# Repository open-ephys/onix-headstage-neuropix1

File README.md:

# ONIX Neuropixels-1.0 Headstage
Serialized, multifunction headstage targeting the [Neuropixels 1.0
probe](https://www.neuropixels.org/probe). This headstage supports:

- Two Neuropixels 1.0 probes
- A BNO055 9-axis IMU for real-time, 3D orientation tracking
- Three TS4231 light to digital converters for real-time, 3D position tracking
  with HTC Vive base stations
- A high performance MAX10 FPGA for real-time processing and probe data
  correction (offset removal and gain correction)

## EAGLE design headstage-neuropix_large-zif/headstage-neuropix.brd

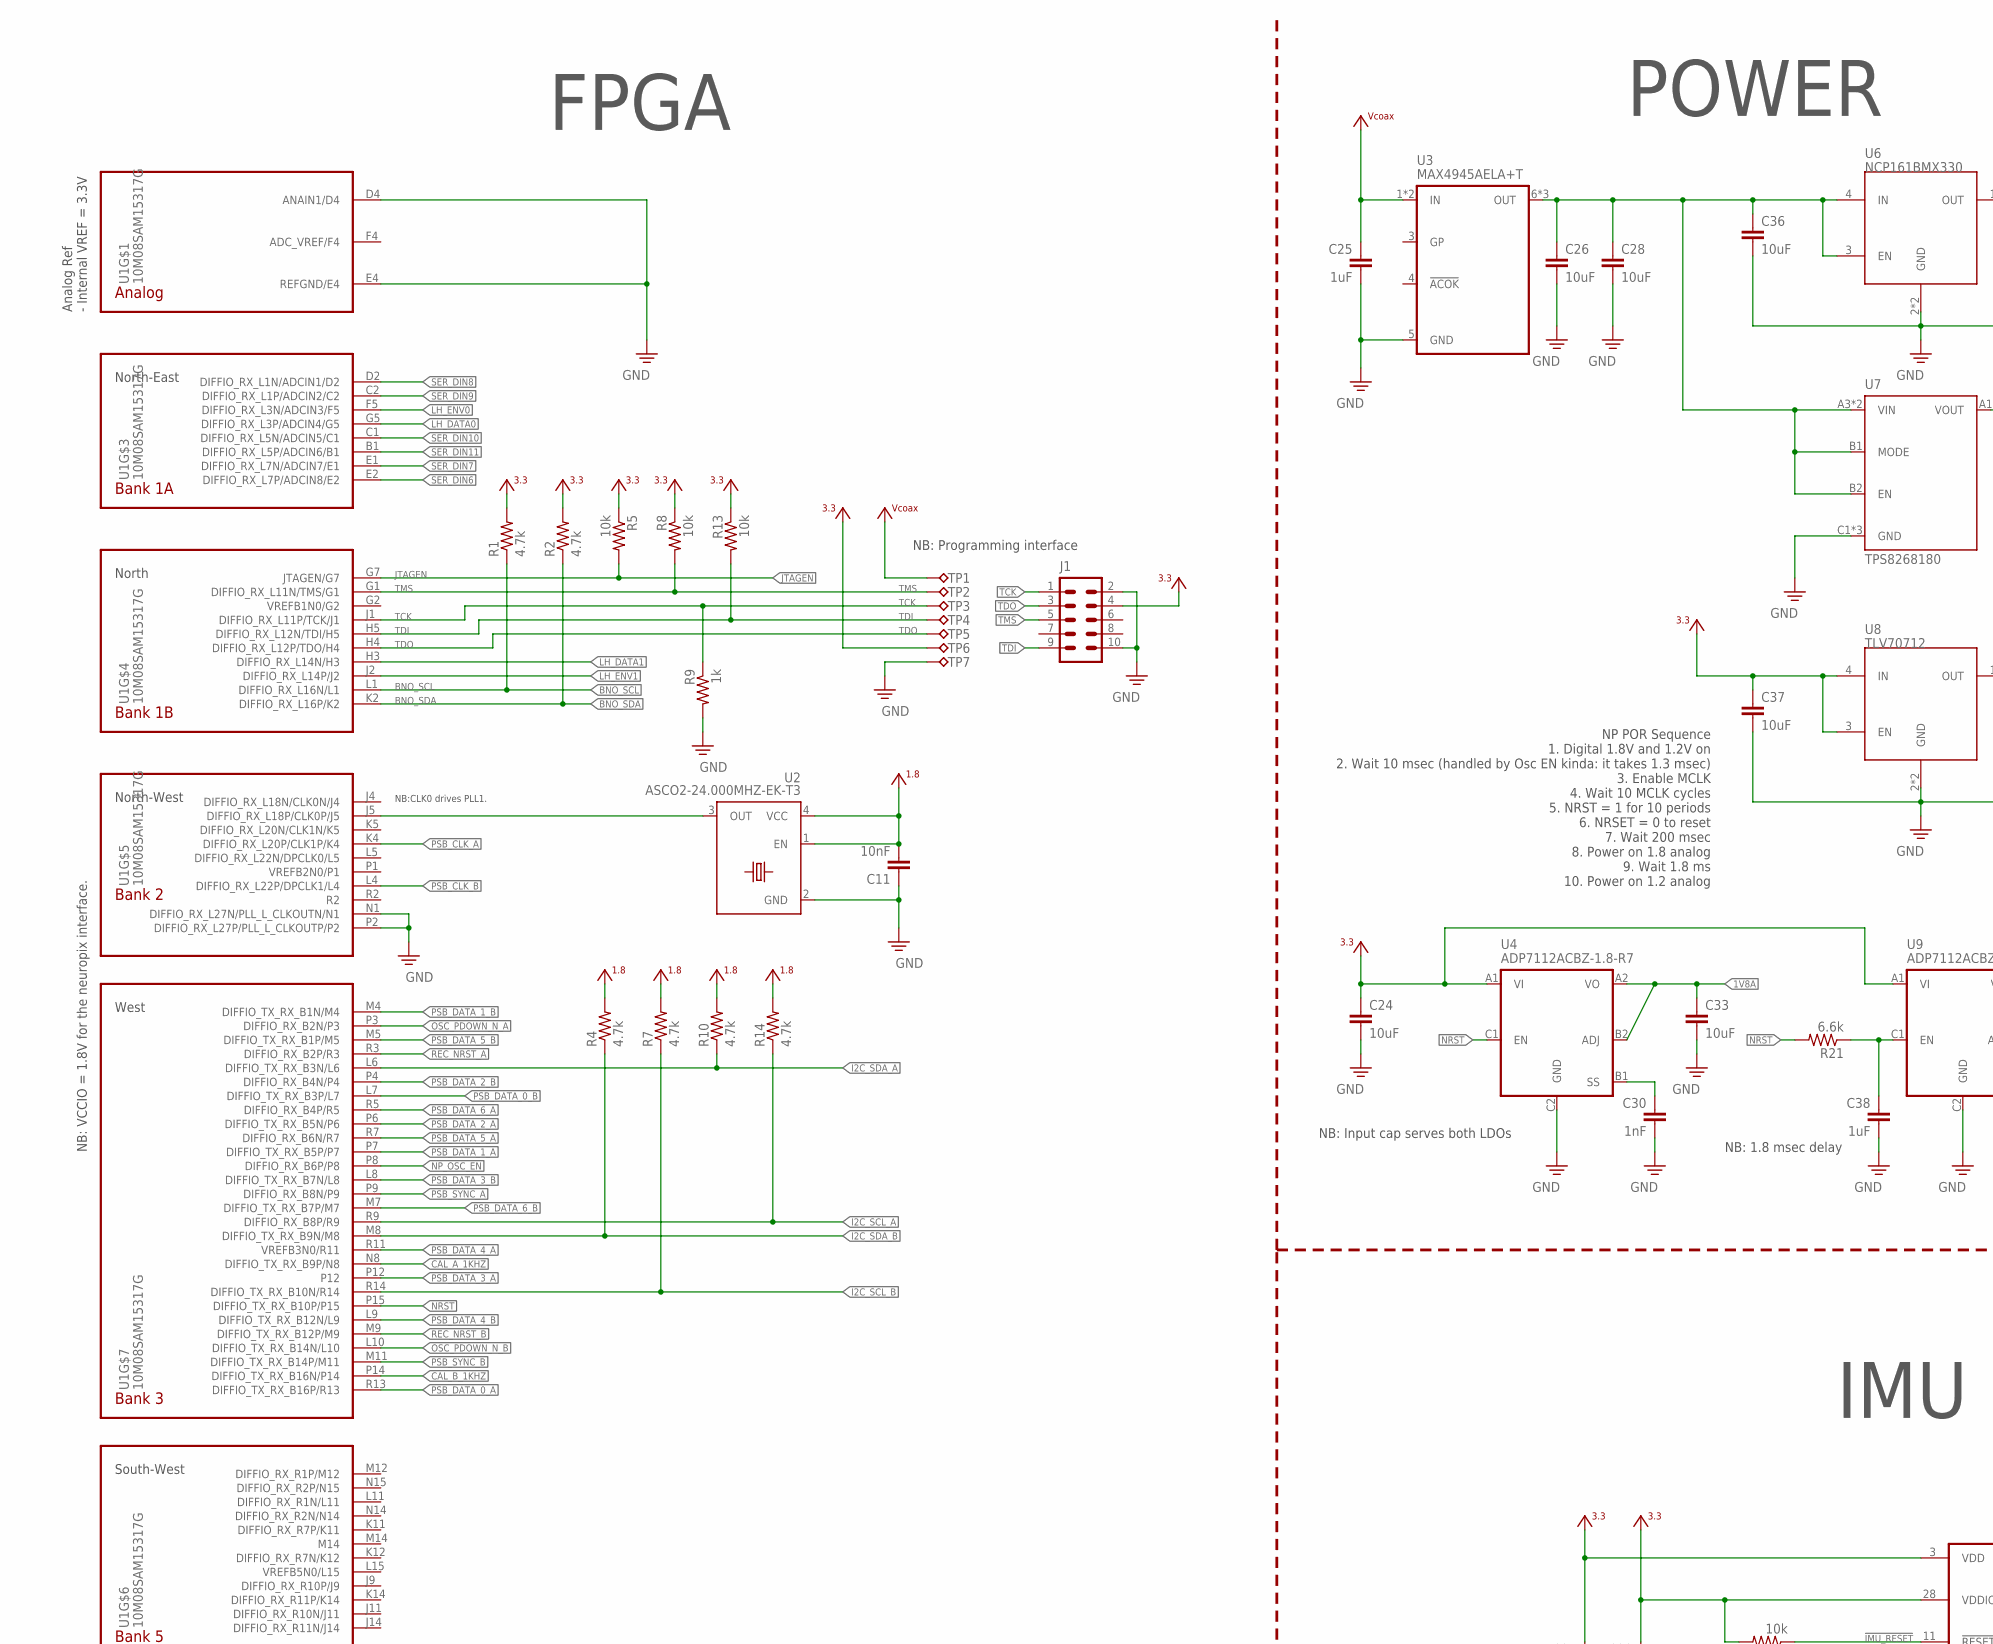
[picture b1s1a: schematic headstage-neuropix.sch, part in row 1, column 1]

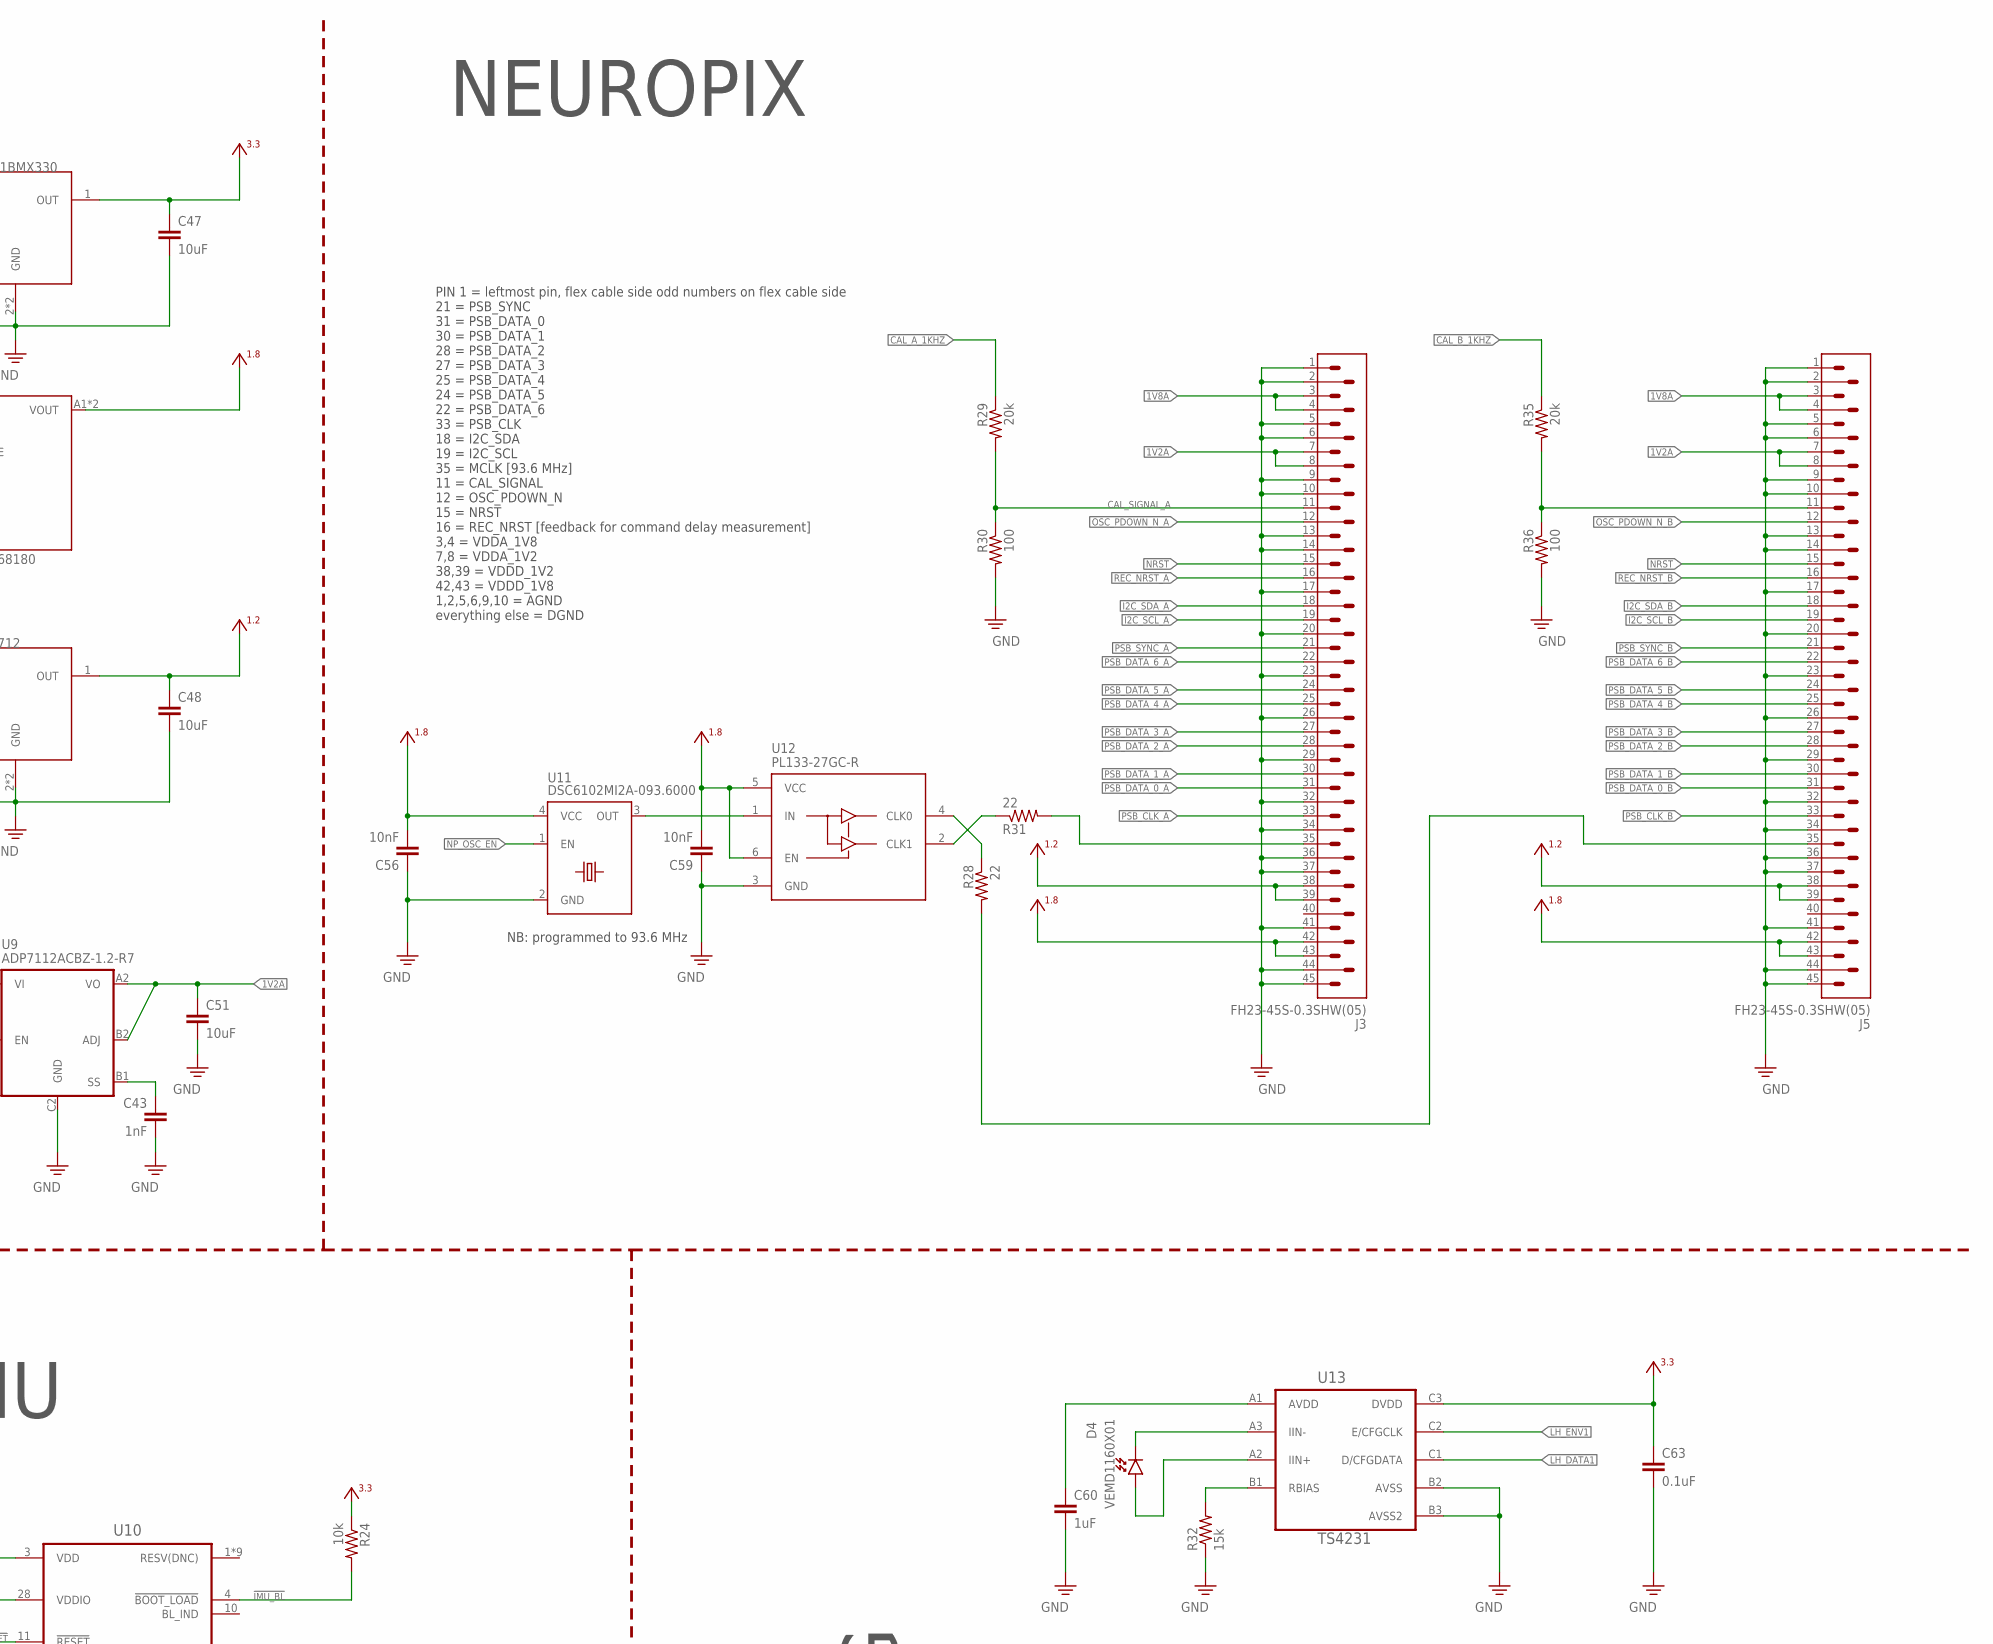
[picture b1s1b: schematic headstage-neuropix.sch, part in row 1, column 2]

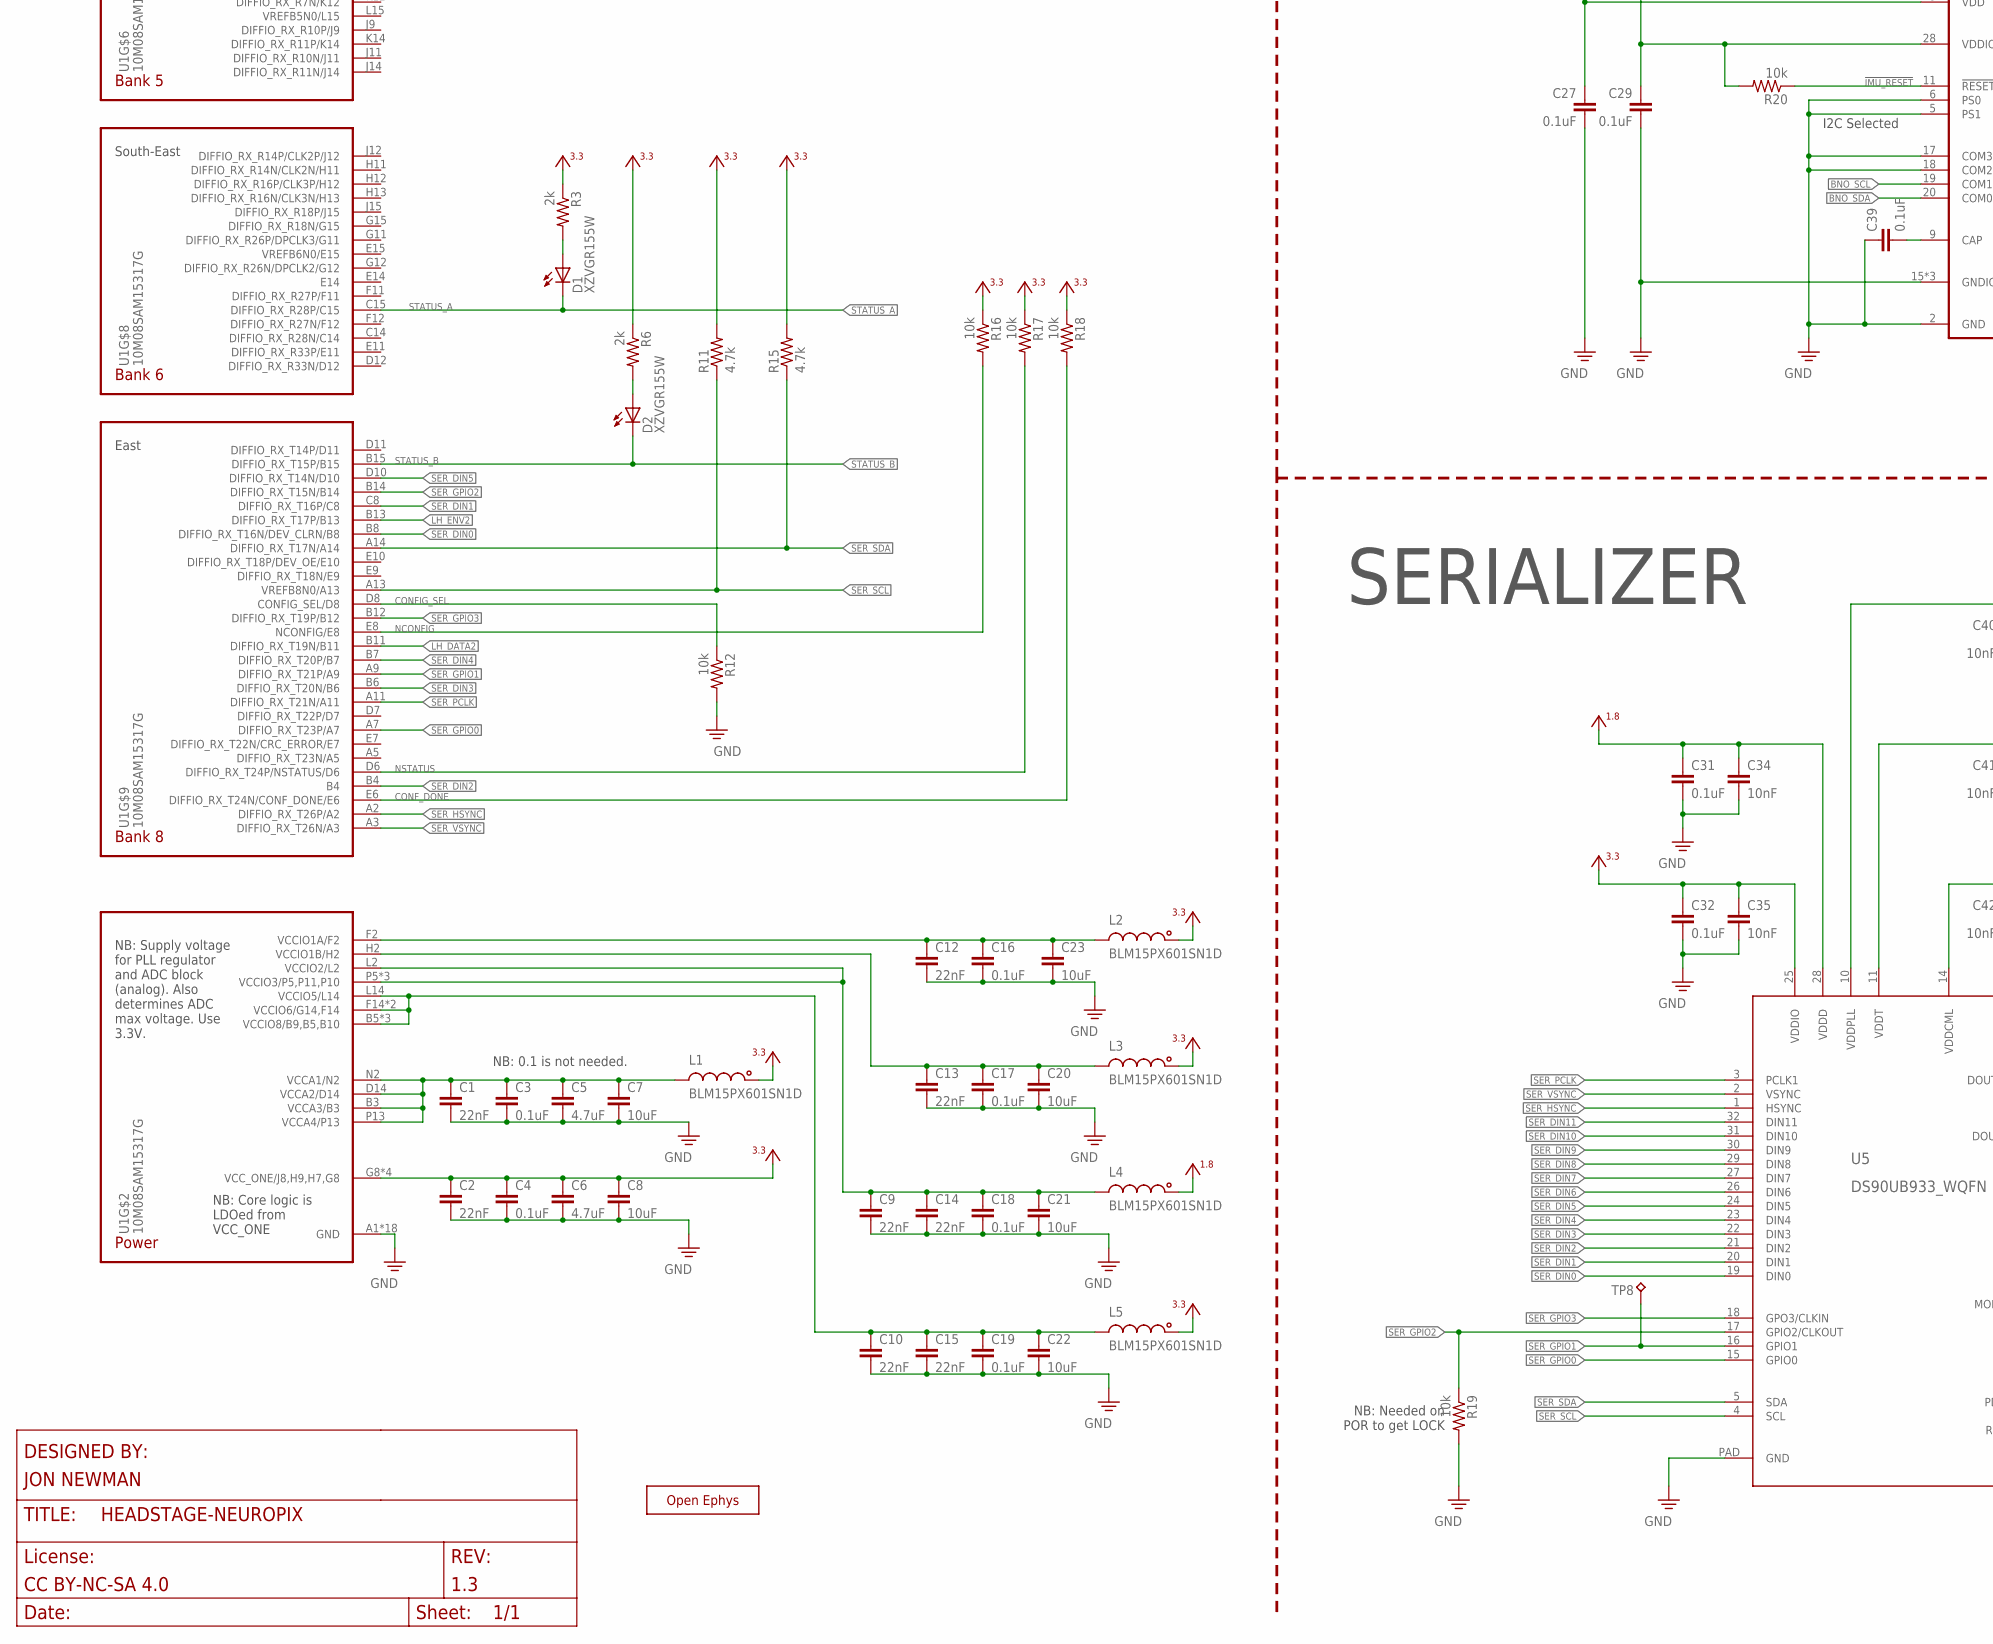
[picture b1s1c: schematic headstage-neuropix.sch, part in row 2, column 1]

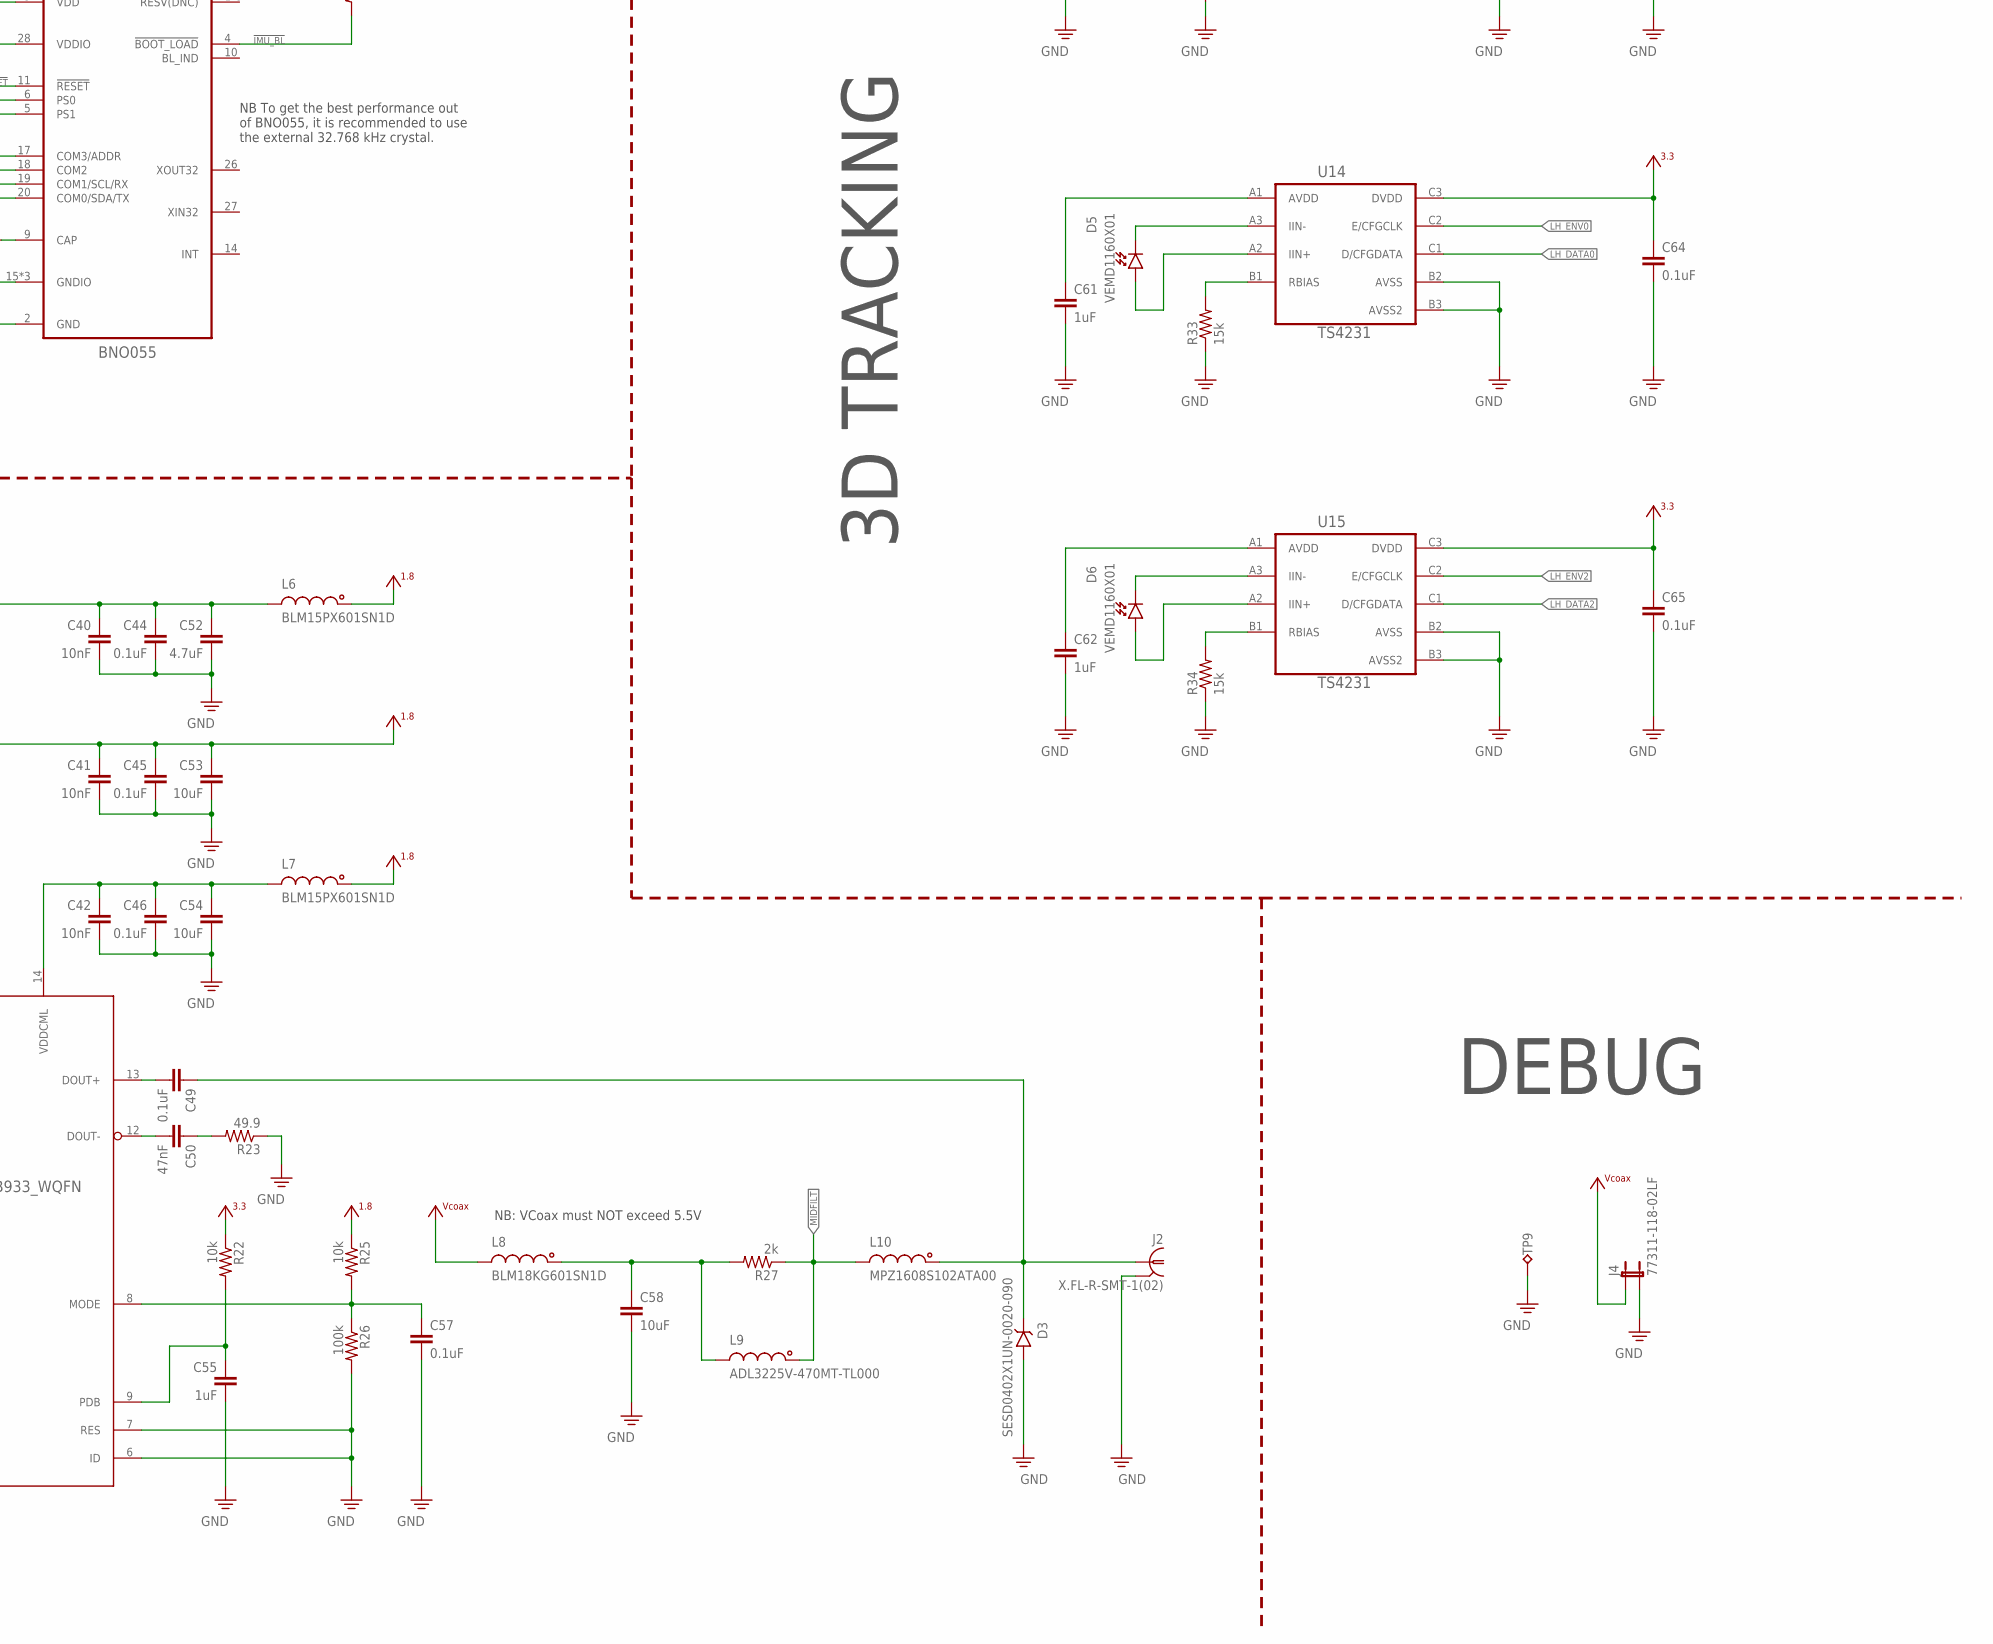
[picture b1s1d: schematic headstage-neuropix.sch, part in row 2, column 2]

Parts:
C1, C2, C9, C10, C12, C13, C14, C15: 22nF; 0201T
C3, C4, C16, C17, C18, C19, C27, C29, C31, C32, C39, C44, C45, C46, C49, C57: 0.1uF; 0201T
C5, C6, C52: 4.7uF; 0402T
C7, C8, C20, C21, C22, C23, C53, C58: 10uF; 0402T
C11, C34, C35, C40, C41, C42, C56, C59: 10nF; 0201T
C24, C26, C28, C33, C36, C37, C47, C48, C51, C54: 10uF; 0402TW
C25, C38, C55: 1uF; 0201T
C30, C43: 1nF; 0201T
C50: 47nF; 0201T
C60, C61, C62: 1uF; 0201T; PARTNO CL03A105MP3ZSNH
C63, C64, C65: 0.1uF; 0201T; PARTNO C0603X5R1C104K030BC
D1, D2: XZVGR155W; LED-0201T
D3: SESD0402X1UN-0020-090; 0402T-DFN
D4, D5, D6: VEMD1160X01; 0805PT-NOSILK
J1: 302-S101; 2X05_IDC
J2: X.FL-R-SMT-1(02); X_FL_R_SMT_1(02)
J3, J5: FH23-45S-0.3SHW(05)
J4: 77311-118-02LF; JP2
L1, L2, L3, L4, L5, L6, L7: BLM15PX601SN1D; 0402T
L8: BLM18KG601SN1D; 0603T
L9: ADL3225V-470MT-TL000; 1210T
L10: MPZ1608S102ATA00; 0603T
R1, R2, R4, R7, R10, R11, R14, R15: 4.7k; 0201T
R3, R6, R27: 2k; 0201T
R5, R8, R12, R13, R16, R17, R18, R19, R20, R22, R24, R25: 10k; 0201T
R9: 1k; 0201T
R21: 6.6k; 0201T
R23: 49.9; 0201T
R26: 100k; 0201T
R28, R31: 22; 0201T
R29, R35: 20k; 0201T
R30, R36: 100; 0201T
R32, R33, R34: 15k; 0201T
TP1, TP2, TP3, TP4, TP5, TP6, TP7: TPTP10R; TP10R
TP8: TPTP09R; TP09R
TP9: TPTP20R; TP20R
U1: 10M08SAM15317G; MBGA153-8X8
U2: ASCO2-24.000MHZ-EK-T3; ASCO
U3: MAX4945AELA+T; UDFN8-2X2
U4: ADP7112ACBZ-1.8-R7; WLCSP6-1X1.2
U5: DS90UB933_WQFN; WQFN32-5X5
U6: NCP161BMX330; X2SON
U7: TPS8268180; MICROSIP9-3X2.3
U8: TLV70712; X2SON
U9: ADP7112ACBZ-1.2-R7; WLCSP6-1X1.2
U10: BNO055; LGA-28-3.8X5.2
U11: DSC6102MI2A-093.6000; VFLGA4-2.0X1.6
U12: PL133-27GC-R; DFN6_2X1.3_PAD
U13, U14, U15: TS4231; WLCSP3X3
X2: OE-LOGO_14X10; OE-LOGO-14X10

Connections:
1V2A: C51.1, J3.7, J3.8, J5.7, J5.8, U9.A2 (VO), U9.B2 (ADJ)
1V8A: C33.1, J3.3, J3.4, J5.3, J5.4, U4.A2 (VO), U4.B2 (ADJ)
24MHZ_P: U1.J5 (DIFFIO_RX_L18P/CLK0P/J5), U2.3 (OUT)
!IMU_BL: R24.2, U10.4 (!BOOT_LOAD)
!IMU_RESET: R20.1, U10.11 (!RESET)
+1V2: C48.1, J3.38, J3.39, J5.38, J5.39, U8.1 (OUT)
+1V8: C11.2, C31.1, C34.1, C41.1, C45.1, C53.1, C56.2, C59.2, J3.42, J3.43, J5.42, J5.43, L4.1, L6.1, L7.1, R4.2, R7.2, R10.2, R14.2, R25.1, U2.1 (EN), U2.4 (VCC), U5.11 (VDDT), U5.28 (VDDD), U7.A1 (VOUT), U7.A2 (VOUT), U11.4 (VCC), U12.5 (VCC), U12.6 (EN)
+3V3: C2.1, C4.1, C6.1, C8.1, C24.1, C27.1, C29.1, C32.1, C35.1, C37.1, C47.1, C63.1, C64.1, C65.1, J1.4, L1.1, L2.1, L3.1, L5.1, R1.2, R2.2, R3.1, R5.1, R6.1, R8.1, R11.2, R13.1, R15.2, R16.1, R17.1, R18.1, R20.2, R22.1, R24.1, TP6.TP, U1.G8 (VCC_ONE/J8,H9,H7,G8), U1.H7 (VCC_ONE/J8,H9,H7,G8), U1.H9 (VCC_ONE/J8,H9,H7,G8), U1.J8 (VCC_ONE/J8,H9,H7,G8), U4.A1 (VI), U5.25 (VDDIO), U6.1 (OUT), U8.3 (EN), U8.4 (IN), U9.A1 (VI), U10.3 (VDD), U10.28 (VDDIO), U13.C3 (DVDD), U14.C3 (DVDD), U15.C3 (DVDD)
BNO_SCL: R1.1, U1.L1 (DIFFIO_RX_L16N/L1), U10.19 (COM1/SCL/RX)
BNO_SDA: R2.1, U1.K2 (DIFFIO_RX_L16P/K2), U10.20 (COM0/SDA/TX)
CAL_A_1KHZ: R29.1, U1.N8 (DIFFIO_TX_RX_B9P/N8)
CAL_B_1KHZ: R35.1, U1.P14 (DIFFIO_TX_RX_B16N/P14)
CAL_SIGNAL_A: J3.11, R29.2, R30.1
CAL_SIGNAL_A1: J5.11, R35.2, R36.1
CONFIG_SEL: R12.1, U1.D8 (CONFIG_SEL/D8)
CONF_DONE: R18.2, U1.E6 (DIFFIO_RX_T24N/CONF_DONE/E6)
GND: C1.2, C2.2, C3.2, C4.2, C5.2, C6.2, C7.2, C8.2, C9.2, C10.2, C11.1, C12.2, C13.2, C14.2, C15.2, C16.2, C17.2, C18.2, C19.2, C20.2, C21.2, C22.2, C23.2, C24.2, C25.2, C26.2, C27.2, C28.2, C29.2, C30.2, C31.2, C32.2, C33.2, C34.2, C35.2, C36.2, C37.2, C38.2, C39.1, C40.2, C41.2, C42.2, C43.2, C44.2, C45.2, C46.2, C47.2, C48.2, C51.2, C52.2, C53.2, C54.2, C55.2, C56.1, C57.2, C58.2, C59.1, C60.2, C61.2, C62.2, C63.2, C64.2, C65.2, D3.A, J1.2, J1.10, J2.P$2 (2), J2.P$3 (2), J2.P$4 (2), J3.1, J3.2, J3.5, J3.6, J3.9, J3.10, J3.13, J3.14, J3.17, J3.20, J3.23, J3.26, J3.29, J3.32, J3.34, J3.36, J3.37, J3.41, J3.44, J3.45, J4.2, J5.1, J5.2, J5.5, J5.6, J5.9, J5.10, J5.13, J5.14, J5.17, J5.20, J5.23, J5.26, J5.29, J5.32, J5.34, J5.36, J5.37, J5.41, J5.44, J5.45, R9.2, R12.2, R19.2, R23.1, R26.2, R30.2, R32.1, R33.1, R34.1, R36.2, TP7.TP, TP9.TP, U1.A1 (GND), U1.A15 (GND), U1.B2 (GND), U1.D4 (ANAIN1/D4), U1.D5 (GND), U1.D9 (GND), U1.E4 (REFGND/E4), U1.E5 (GND), U1.E12 (GND), U1.G4 (GND), U1.G9 (GND), U1.H8 (GND), U1.H14 (GND), U1.J7 (GND), U1.L12 (GND), U1.M2 (GND), U1.M6 (GND), U1.M10 (GND), U1.N1 (DIFFIO_RX_L27N/PLL_L_CLKOUTN/N1), U1.P2 (DIFFIO_RX_L27P/PLL_L_CLKOUTP/P2), U1.R1 (GND), U1.R15 (GND), U2.2 (GND), U3.5 (GND), U4.C2 (GND), U5.6 (ID), U5.7 (RES), U5.PAD (GND), U6.2 (GND), U6.PAD (GND), U7.C1 (GND), U7.C2 (GND), U7.C3 (GND), U8.2 (GND), U8.PAD (GND), U9.C2 (GND), U10.2 (GND), U10.5 (PS1), U10.6 (PS0), U10.15 (GNDIO), U10.16 (GNDIO), U10.17 (COM3/ADDR), U10.18 (COM2), U10.25 (GNDIO), U11.2 (GND), U12.3 (GND), U13.B2 (AVSS), U13.B3 (AVSS2), U14.B2 (AVSS), U14.B3 (AVSS2), U15.B2 (AVSS), U15.B3 (AVSS2)
I2C_SCL_A: J3.19, R14.1, U1.R9 (DIFFIO_RX_B8P/R9)
I2C_SCL_B: J5.19, R7.1, U1.R14 (DIFFIO_TX_RX_B10N/R14)
I2C_SDA_A: J3.18, R10.1, U1.L6 (DIFFIO_TX_RX_B3N/L6)
I2C_SDA_B: J5.18, R4.1, U1.M8 (DIFFIO_TX_RX_B9N/M8)
JTAGEN: R5.2, U1.G7 (JTAGEN/G7)
LH_DATA0: U1.G5 (DIFFIO_RX_L3P/ADCIN4/G5), U14.C1 (D/CFGDATA)
LH_DATA1: U1.H3 (DIFFIO_RX_L14N/H3), U13.C1 (D/CFGDATA)
LH_DATA2: U1.B11 (DIFFIO_RX_T19N/B11), U15.C1 (D/CFGDATA)
LH_ENV0: U1.F5 (DIFFIO_RX_L3N/ADCIN3/F5), U14.C2 (E/CFGCLK)
LH_ENV1: U1.J2 (DIFFIO_RX_L14P/J2), U13.C2 (E/CFGCLK)
LH_ENV2: U1.B13 (DIFFIO_RX_T17P/B13), U15.C2 (E/CFGCLK)
MIDFILT: L9.1, L10.2, R27.1
unnamed: U11.3 (OUT), U12.1 (IN)
unnamed: R28.1, U12.4 (CLK0)
unnamed: J3.35, R31.2
unnamed: C13.1, C17.1, C20.1, L3.2, U1.H2 (VCCIO1B/H2)
unnamed: J5.35, R28.2
unnamed: R31.1, U12.2 (CLK1)
unnamed: D4.C, U13.A3 (IIN-)
unnamed: D4.A, U13.A2 (IIN+)
unnamed: R32.2, U13.B1 (RBIAS)
unnamed: C60.1, U13.A1 (AVDD)
unnamed: C58.1, L8.1, L9.2, R27.2
unnamed: D5.C, U14.A3 (IIN-)
unnamed: D5.A, U14.A2 (IIN+)
unnamed: R33.2, U14.B1 (RBIAS)
unnamed: D6.C, U15.A3 (IIN-)
unnamed: D6.A, U15.A2 (IIN+)
unnamed: C49.2, U5.13 (DOUT+)
unnamed: R34.2, U15.B1 (RBIAS)
unnamed: C55.1, R22.2, U5.9 (PDB)
unnamed: C50.2, U5.12 (DOUT-)
unnamed: C50.1, R23.2
unnamed: C57.1, R25.2, R26.1, U5.8 (MODE)
unnamed: C40.1, C44.1, C52.1, L6.2, U5.10 (VDDPLL)
unnamed: C42.1, C46.1, C54.1, L7.2, U5.14 (VDDCML)
unnamed: C61.1, U14.A1 (AVDD)
unnamed: C62.1, U15.A1 (AVDD)
unnamed: C26.1, C28.1, C36.1, U3.6 (OUT), U3.7 (OUT), U3.8 (OUT), U6.3 (EN), U6.4 (IN), U7.A3 (VIN), U7.B1 (MODE), U7.B2 (EN), U7.B3 (VIN)
unnamed: C30.1, U4.B1 (SS)
unnamed: C43.1, U9.B1 (SS)
unnamed: C38.1, R21.1, U9.C1 (EN)
unnamed: C39.2, U10.9 (CAP)
unnamed: D2.2 (A), R6.2
unnamed: D1.2 (A), R3.2
NCONFIG: R16.2, U1.E8 (NCONFIG/E8)
NP_OSC_EN: U1.P8 (DIFFIO_RX_B6P/P8), U11.1 (EN)
NRST: J3.15, J5.15, R21.2, U1.P15 (DIFFIO_TX_RX_B10P/P15), U4.C1 (EN)
NSTATUS: R17.2, U1.D6 (DIFFIO_RX_T24P/NSTATUS/D6)
OSC_PDOWN_N_A: J3.12, U1.P3 (DIFFIO_RX_B2N/P3)
OSC_PDOWN_N_B: J5.12, U1.L10 (DIFFIO_TX_RX_B14N/L10)
PSB_CLK_A: J3.33, U1.K4 (DIFFIO_RX_L20P/CLK1P/K4)
PSB_CLK_B: J5.33, U1.L4 (DIFFIO_RX_L22P/DPCLK1/L4)
PSB_DATA_0_A: J3.31, U1.R13 (DIFFIO_TX_RX_B16P/R13)
PSB_DATA_0_B: J5.31, U1.L7 (DIFFIO_TX_RX_B3P/L7)
PSB_DATA_1_A: J3.30, U1.P7 (DIFFIO_TX_RX_B5P/P7)
PSB_DATA_1_B: J5.30, U1.M4 (DIFFIO_TX_RX_B1N/M4)
PSB_DATA_2_A: J3.28, U1.P6 (DIFFIO_TX_RX_B5N/P6)
PSB_DATA_2_B: J5.28, U1.P4 (DIFFIO_RX_B4N/P4)
PSB_DATA_3_A: J3.27, U1.P12
PSB_DATA_3_B: J5.27, U1.L8 (DIFFIO_TX_RX_B7N/L8)
PSB_DATA_4_A: J3.25, U1.R11 (VREFB3N0/R11)
PSB_DATA_4_B: J5.25, U1.L9 (DIFFIO_TX_RX_B12N/L9)
PSB_DATA_5_A: J3.24, U1.R7 (DIFFIO_RX_B6N/R7)
PSB_DATA_5_B: J5.24, U1.M5 (DIFFIO_TX_RX_B1P/M5)
PSB_DATA_6_A: J3.22, U1.R5 (DIFFIO_RX_B4P/R5)
PSB_DATA_6_B: J5.22, U1.M7 (DIFFIO_TX_RX_B7P/M7)
PSB_SYNC_A: J3.21, U1.P9 (DIFFIO_RX_B8N/P9)
PSB_SYNC_B: J5.21, U1.M11 (DIFFIO_TX_RX_B14P/M11)
REC_NRST_A: J3.16, U1.R3 (DIFFIO_RX_B2P/R3)
REC_NRST_B: J5.16, U1.M9 (DIFFIO_TX_RX_B12P/M9)
SER_DIN0: U1.B8 (DIFFIO_RX_T16N/DEV_CLRN/B8), U5.19 (DIN0)
SER_DIN1: U1.C8 (DIFFIO_RX_T16P/C8), U5.20 (DIN1)
SER_DIN2: U1.B4, U5.21 (DIN2)
SER_DIN3: U1.B6 (DIFFIO_RX_T20N/B6), U5.22 (DIN3)
SER_DIN4: U1.B7 (DIFFIO_RX_T20P/B7), U5.23 (DIN4)
SER_DIN5: U1.D10 (DIFFIO_RX_T14N/D10), U5.24 (DIN5)
SER_DIN6: U1.E2 (DIFFIO_RX_L7P/ADCIN8/E2), U5.26 (DIN6)
SER_DIN7: U1.E1 (DIFFIO_RX_L7N/ADCIN7/E1), U5.27 (DIN7)
SER_DIN8: U1.D2 (DIFFIO_RX_L1N/ADCIN1/D2), U5.29 (DIN8)
SER_DIN9: U1.C2 (DIFFIO_RX_L1P/ADCIN2/C2), U5.30 (DIN9)
SER_DIN10: U1.C1 (DIFFIO_RX_L5N/ADCIN5/C1), U5.31 (DIN10)
SER_DIN11: U1.B1 (DIFFIO_RX_L5P/ADCIN6/B1), U5.32 (DIN11)
SER_GPIO0: U1.A7 (DIFFIO_RX_T23P/A7), U5.15 (GPIO0)
SER_GPIO1: TP8.TP, U1.A9 (DIFFIO_RX_T21P/A9), U5.16 (GPIO1)
SER_GPIO2: R19.1, U1.B14 (DIFFIO_RX_T15N/B14), U5.17 (GPIO2/CLKOUT)
SER_GPIO3: U1.B12 (DIFFIO_RX_T19P/B12), U5.18 (GPO3/CLKIN)
SER_HSYNC: U1.A2 (DIFFIO_RX_T26P/A2), U5.1 (HSYNC)
SER_PCLK: U1.A11 (DIFFIO_RX_T21N/A11), U5.3 (PCLK1)
SER_SCL: R11.1, U1.A13 (VREFB8N0/A13), U5.4 (SCL)
SER_SDA: R15.1, U1.A14 (DIFFIO_RX_T17N/A14), U5.5 (SDA)
SER_VSYNC: U1.A3 (DIFFIO_RX_T26N/A3), U5.2 (VSYNC)
SIGOUT: C49.1, D3.C, J2.P$1 (1), L10.1
STATUS_A: D1.1 (C), U1.C15 (DIFFIO_RX_R28P/C15)
STATUS_B: D2.1 (C), U1.B15 (DIFFIO_RX_T15P/B15)
TCK: J1.1, R9.1, TP3.TP, U1.J1 (DIFFIO_RX_L11P/TCK/J1)
TDI: J1.9, R13.2, TP4.TP, U1.H5 (DIFFIO_RX_L12N/TDI/H5)
TDO: J1.3, TP5.TP, U1.H4 (DIFFIO_RX_L12P/TDO/H4)
TMS: J1.5, R8.2, TP2.TP, U1.G1 (DIFFIO_RX_L11N/TMS/G1)
VCCA: C1.1, C3.1, C5.1, C7.1, L1.2, U1.B3 (VCCA3/B3), U1.D14 (VCCA2/D14), U1.N2 (VCCA1/N2), U1.P13 (VCCA4/P13)
VCCIO: C10.1, C15.1, C19.1, C22.1, L5.2, U1.B5 (VCCIO8/B9,B5,B10), U1.B9 (VCCIO8/B9,B5,B10), U1.B10 (VCCIO8/B9,B5,B10), U1.F14 (VCCIO6/G14,F14), U1.G14 (VCCIO6/G14,F14), U1.L14 (VCCIO5/L14)
VCCIO2: C9.1, C14.1, C18.1, C21.1, L4.2, U1.L2 (VCCIO2/L2), U1.P5 (VCCIO3/P5,P11,P10), U1.P10 (VCCIO3/P5,P11,P10), U1.P11 (VCCIO3/P5,P11,P10)
VCCIOA: C12.1, C16.1, C23.1, L2.2, U1.F2 (VCCIO1A/F2)
VCOAX: C25.1, J4.1, L8.2, TP1.TP, U3.1 (IN), U3.2 (IN)

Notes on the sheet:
NB: VCoax must NOT exceed 5.5V
SERIALIZER
POWER
NEUROPIX
DEBUG
PIN 1 = leftmost pin, flex cable side odd numbers on flex cable side 21 = PSB_SYNC 31 = PSB_DATA_0 30 = PSB_DATA_1 28 = PSB_DATA_2 27 = PSB_DATA_3 25 = PSB_DATA_4 24 = PSB_DATA_5 22 = PSB_DATA_6 33 = PSB_CLK 18 = I2C_SDA 19 = I2C_SCL 35 = MCLK [93.6 MHz] 11 = CAL_SIGNAL 12 = OSC_PDOWN_N 15 = NRST 1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
NB: Core logic is LDOed from VCC_ONE
NB: Supply voltage for PLL regulator and ADC block (analog). Also determines ADC max voltage. Use 3.3V.
NB: VCCIO = 1.8V for the neuropix interface.
FPGA
South-East
East
South-West
West
North-West
North
North-East
Analog Ref - Internal VREF = 3.3V
NB: Programming interface
NB: 0.1 is not needed.
NB:CLK0 drives PLL1.
IMU
I2C Selected
NB To get the best performance out of BNO055, it is recommended to use the external 32.768 kHz crystal.
3D TRACKING
NB: programmed to 93.6 MHz
NP POR Sequence 1. Digital 1.8V and 1.2V on 2. Wait 10 msec (handled by Osc EN kinda: it takes 1.3 msec) 3. Enable MCLK 4. Wait 10 MCLK cycles 5. NRST = 1 for 10 periods 6. NRSET = 0 to reset 7. Wait 200 msec 8. Power on 1.8 analog 9. Wait 1.8 ms 10. Power on 1.2 analog
NB: 1.8 msec delay
NB: Input cap serves both LDOs
NB: Needed on POR to get LOCK

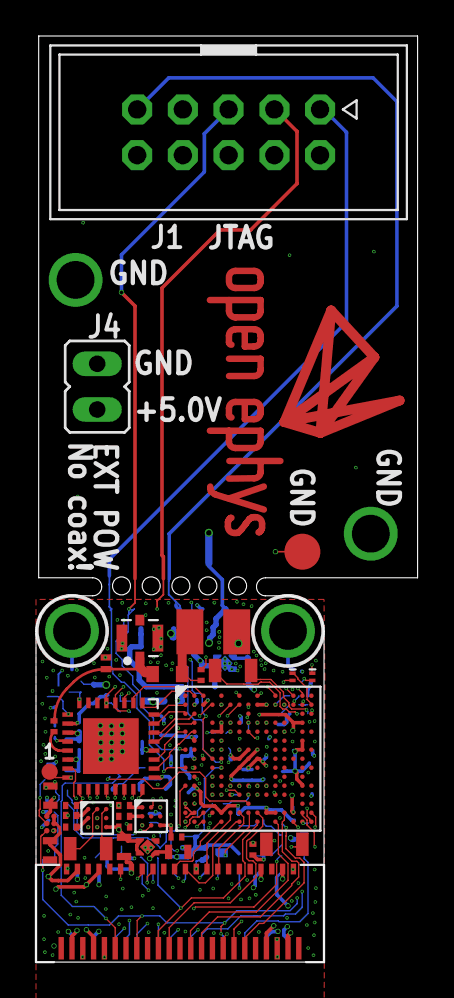
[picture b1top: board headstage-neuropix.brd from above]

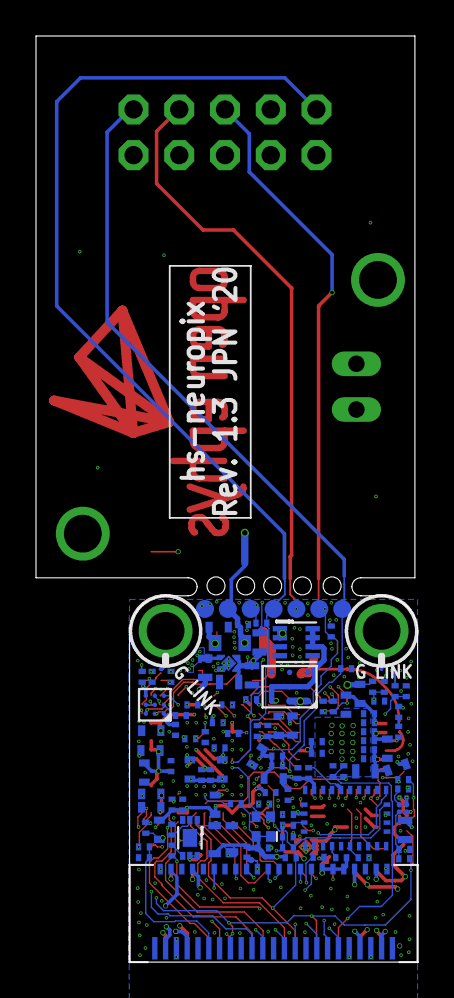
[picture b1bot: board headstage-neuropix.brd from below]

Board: 6 copper layers, 21.2 x 51.5 mm, 147 parts (112 on the bottom side), 121 nets.

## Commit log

2019-08-08 Initial rough component placement for neuropix test headstage
2019-08-08 Added ZIF conn and did some basic layout
    Hirose FH23-45S-0.3SHW(05) ( HFQ645CT-ND ) looks like it will work
2019-08-09 Added LMK61E2
    Should solve the issue of how to make 93.6 MHz, but is pretty huge
2019-08-10 Some more layout on neuropix headstage
    - Switched to large MAX10
    - started to assign some pins
2019-08-12 Cleaned up and renamed neuropix headstage
2019-08-12 Moved some things on the neuropix HS
    jon take over
2019-08-15 headstage-neuropix rev 1.0
    - Should conform to JLCPCB 6-layer DRU
2019-08-18 Revisions to headstage-neuropix following group review
    - The programmable oscillator was removed because the MCLK signal is not
    needed by the FPGA. It was replaced with a factory programmed 93.6 MHz
    silicon oscillator that is feed directly into MCLK pin via RC low-pass
    filter that matches that on the IMEC headstage
    - Added the BNO055 IMU
    - Other small changes to silkscreen and debug routing (e.g. remove
2019-08-19 Fixed flat-flex connector part number on headstage-neuropix
    - Also, updated PDF of schematic
2019-09-27 headstage-neuropix rev. 1.1
    - Changes after testing rev. 1.0
    - Coax connection moved away from the inductors to give more wiggle room
    during connection
    - 1.2 Vreg now has Vin = 3.3V instead of 1.8, which was non functional
    - Pullups added to NP i2c lines
    - Bottom side debug ground connections added
2019-10-28 headstage-neuropix rev 1.2
    - Fix a couple issues found during assembly of revision 1.1
    - Move C and L pads containing 3.3V and GND further appart to prevent
    shorting during reflow
    - Add Vcoax measurement to FPGA's ADC
    - 0402 15 uF pads are wider by 0.2 mm
    - Move bypass caps further away from LDOs for ease of assembly
2019-12-07 headstage-neuropix rev 1.2
    - Dual neuropixels probe support
    - 2X HTC Vive receivers
    - Many changes made for reliability of manufacturing
2020-02-27 Revision 1.2 of headstage-neuropix
    - Routed all GPIO from serializer to FPGA
    - Inner layers are now 3 mil trace space
    - via-reduce just like headstage-64
2020-03-09 Final headstage-neuropix rev. 1.2
    - BOM simplification while updating the google sheet
    - Small PCB changes
2020-05-22 Added third lighthouse receiver to headstage-neuropix
    - I'm now sending this to speedy for a quote
2020-05-30 Minor improvements to headstage-neuropix rev 1.2
    - Final changes before production
    - Minor BOM simplification
2020-06-02 More updates to headstage-neuropix after review from Speedy
    - Many bottom side pads moved apart to allow solder mask in between and
    to prevent shorts
2020-08-28 Move entire repository to CC BY-NC-SA 4.0
2021-02-15 headstage-neuropix rev. 1.3
    - Fixes several issues found during testing or revision 1.2
    - Analog power to neurpixels probe is now isolated using LC filter from
    digital power
    - 93.6 MHz osc gets power from 1.8V instead of 3.3. Footprint fixed.
    - Vcoax has more bulk capacitance now
    - Serializer has capacitance on its PDN pin as recormmended to get POR
2021-02-15 Added MEMS oscillator datasheet
2021-05-29 headstage-neuropix rev. 1.3
    - Addresses several more issues encountered during extensive testing of
    rev. 1.2
    - Analog rails of probes provided by dedicated LDOs that respect the
    complex POR sequence required by the probes
    - The clock enable for the dual clock buffer for each probe is tied high
    instead of being driven by the clock input (!)
2021-05-29 Standard ZIF version of headstage-neuropix rev 1.3
    - Added a second version of the headstage that uses the smaller,
    IMEC-specified ZIF connector
    - Reorganized the folder a bit to support this change
2021-05-29 Spelling correction in headstage-neuropix/README
2021-05-30 Updated BOM for revision 1.3
    - External on google-sheet. Link added to READMEs for each board
    version.
    - Schematics updated to reflect the BOM.
    - Added SMD mount information
    - Added .gitignore and .gitattributes for LFS
2021-05-30 Moved X.FL coax connector up 0.5 mm following OEPS feedback
    - Allows more tolerance for passives under it
    - Did this for both headstage variants
2021-07-18 Update .gitignore
    - Remove questionable descriptions in comments
2021-07-28 Small layout changes after communicating with Speedy
    - Reduced solder mask openings a bit
    - Other small changes
2021-08-05 Correct tPlace/tStop mixup for ADP7112's
    - Solder pads had tPlace instead of tStop so there would have been
    silkscreen on the pads
2021-08-09 Revision 1.3
    - Update SMD mount files for produced design
    - Add the production files provided by speedy to the repository
2021-08-09 Repository reorganization
    - Moved all design files into the headstage-neuropix1 directory
    - Added image of rev 1.2 with probes attached
2021-08-10 Added stencil gerbers to production files.
2021-09-01 Add license
    - CC BY-NC-SA 4.0
